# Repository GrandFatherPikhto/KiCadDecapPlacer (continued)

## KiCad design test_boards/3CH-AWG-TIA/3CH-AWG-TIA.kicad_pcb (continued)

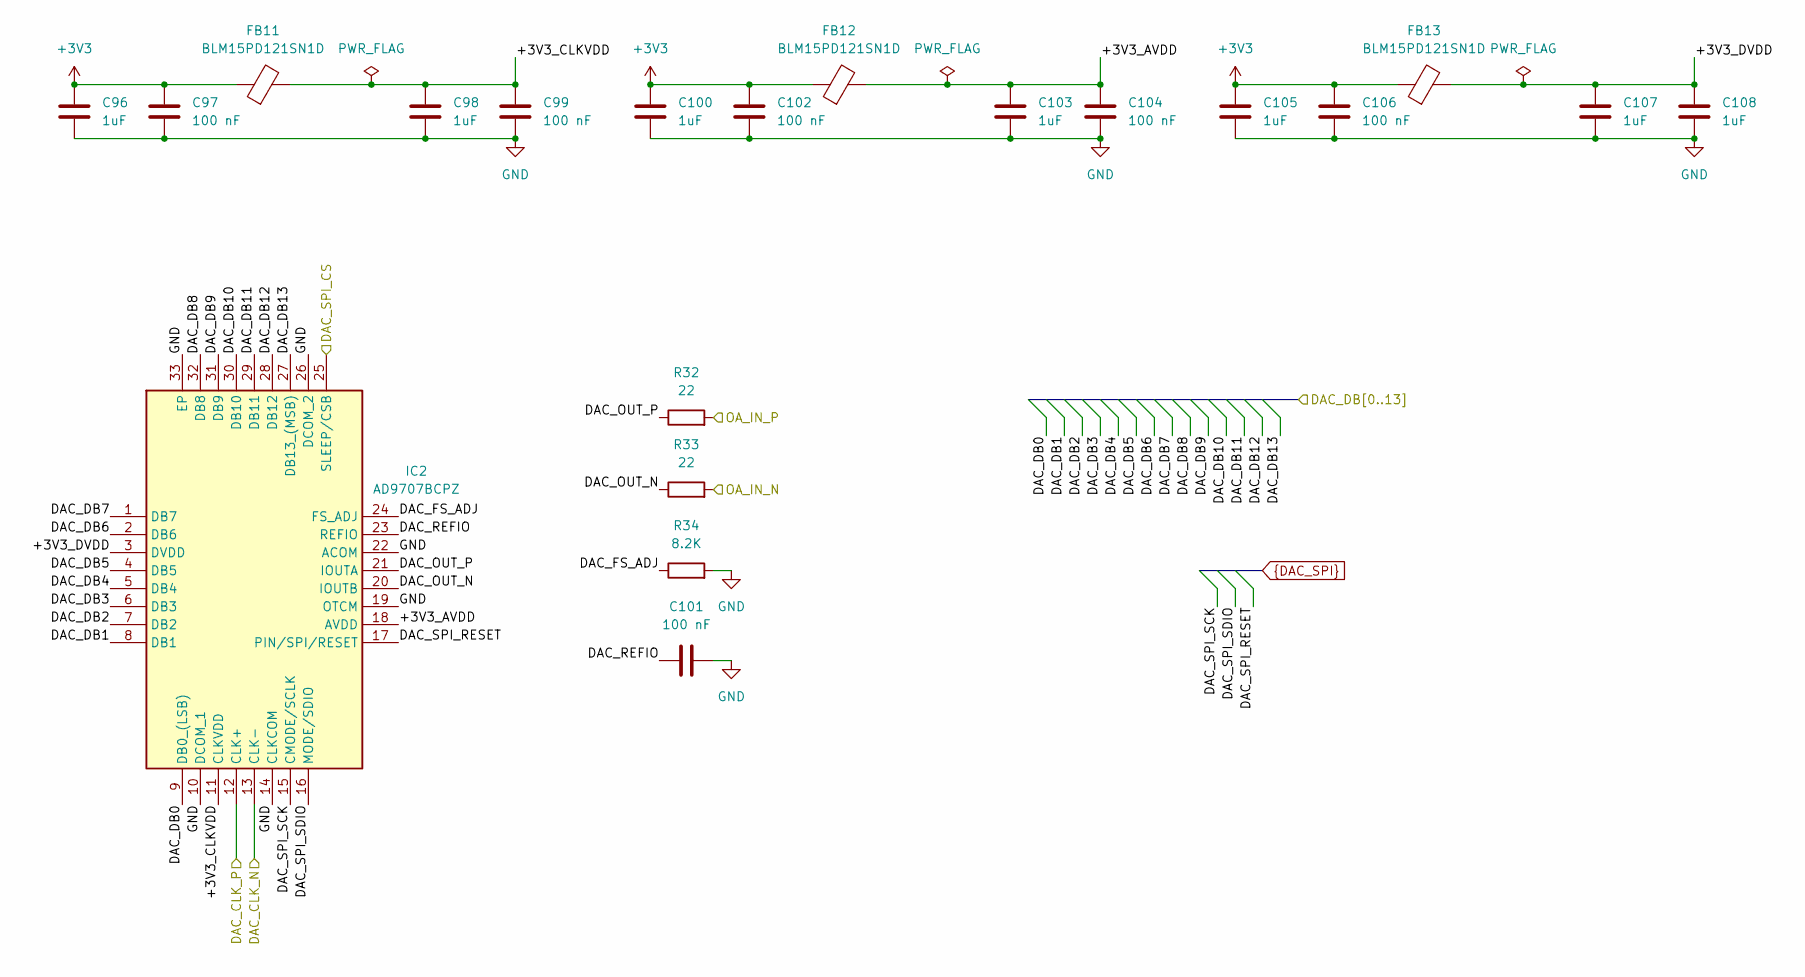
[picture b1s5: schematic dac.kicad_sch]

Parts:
C96, C98, C100, C103, C105, C107, C108: 1uF; C_0603_1608Metric_Pad1.08x0.95mm_HandSolder
C97, C99, C102, C104, C106: 100 nF; C_0402_1005Metric_Pad0.74x0.62mm_HandSolder
C101: 100 nF; C_0603_1608Metric_Pad1.08x0.95mm_HandSolder
FB11, FB12, FB13: BLM15PD121SN1D; L_0402_1005Metric
IC2: AD9707BCPZ; QFN50P500X500X80-33N-D; Manufacturer_Part_Number AD9705BCPZ; Mouser Part Number 584-AD9705BCPZ
R32, R33: 22; R_0402_1005Metric_Pad0.72x0.64mm_HandSolder
R34: 8.2K; R_0402_1005Metric_Pad0.72x0.64mm_HandSolder

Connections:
+3V3: C96.1, C97.1, C100.1, C102.1, C105.1, C106.1, FB11.1, FB12.1, FB13.1; also elsewhere on the board
/Channel_0/DAC/+3V3_AVDD: C103.1, C104.1, FB12.2, IC2.18 (AVDD)
/Channel_0/DAC/+3V3_CLKVDD: C98.1, C99.1, FB11.2, IC2.11 (CLKVDD)
/Channel_0/DAC/+3V3_DVDD: C107.1, C108.1, FB13.2, IC2.3 (DVDD)
/Channel_0/DAC/DAC_FS_ADJ: IC2.24 (FS_ADJ), R34.1
/Channel_0/DAC/DAC_OUT_N: IC2.20 (IOUTB), R33.1
/Channel_0/DAC/DAC_OUT_P: IC2.21 (IOUTA), R32.1
/Channel_0/DAC/DAC_REFIO: C101.1, IC2.23 (REFIO)
/Channel_0/DAC_CLK_N: IC2.13 (CLK-); also elsewhere on the board
/Channel_0/DAC_CLK_P: IC2.12 (CLK+); also elsewhere on the board
/Channel_0/DAC_DB0: IC2.9 (DB0_(LSB)); also elsewhere on the board
/Channel_0/DAC_DB1: IC2.8 (DB1); also elsewhere on the board
/Channel_0/DAC_DB2: IC2.7 (DB2); also elsewhere on the board
/Channel_0/DAC_DB3: IC2.6 (DB3); also elsewhere on the board
/Channel_0/DAC_DB4: IC2.5 (DB4); also elsewhere on the board
/Channel_0/DAC_DB5: IC2.4 (DB5); also elsewhere on the board
/Channel_0/DAC_DB6: IC2.2 (DB6); also elsewhere on the board
/Channel_0/DAC_DB7: IC2.1 (DB7); also elsewhere on the board
/Channel_0/DAC_DB8: IC2.32 (DB8); also elsewhere on the board
/Channel_0/DAC_DB9: IC2.31 (DB9); also elsewhere on the board
/Channel_0/DAC_DB10: IC2.30 (DB10); also elsewhere on the board
/Channel_0/DAC_DB11: IC2.29 (DB11); also elsewhere on the board
/Channel_0/DAC_DB12: IC2.28 (DB12); also elsewhere on the board
/Channel_0/DAC_DB13: IC2.27 (DB13_(MSB)); also elsewhere on the board
/Channel_0/OpAmp/OA_IN_N: R33.2; also elsewhere on the board
/Channel_0/OpAmp/OA_IN_P: R32.2; also elsewhere on the board
/FPGA/DAC0_SPI_CS: IC2.25 (SLEEP/CSB); also elsewhere on the board
DAC_SPI_RESET: IC2.17 (PIN/SPI/RESET); also elsewhere on the board
DAC_SPI_SCK: IC2.15 (CMODE/SCLK); also elsewhere on the board
DAC_SPI_SDIO: IC2.16 (MODE/SDIO); also elsewhere on the board
GND: C96.2, C97.2, C98.2, C99.2, C100.2, C101.2, C102.2, C103.2, C104.2, C105.2, C106.2, C107.2, C108.2, IC2.10 (DCOM_1), IC2.14 (CLKCOM), IC2.19 (OTCM), IC2.22 (ACOM), IC2.26 (DCOM_2), IC2.33 (EP), R34.2; also elsewhere on the board

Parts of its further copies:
C130, C132, C134, C137, C139, C141, C142, C164, C166, C168, C171, C173, C175, C176: 1uF; C_0603_1608Metric_Pad1.08x0.95mm_HandSolder
C131, C133, C136, C138, C140, C165, C167, C170, C172, C174: 100 nF; C_0402_1005Metric_Pad0.74x0.62mm_HandSolder
C135, C169: 100 nF; C_0603_1608Metric_Pad1.08x0.95mm_HandSolder
FB18, FB19, FB20, FB25, FB26, FB27: BLM15PD121SN1D; L_0402_1005Metric
IC3, IC4: AD9707BCPZ; QFN50P500X500X80-33N-D; Manufacturer_Part_Number AD9705BCPZ; Mouser Part Number 584-AD9705BCPZ
R48, R49, R64, R65: 22; R_0402_1005Metric_Pad0.72x0.64mm_HandSolder
R50, R66: 8.2K; R_0402_1005Metric_Pad0.72x0.64mm_HandSolder

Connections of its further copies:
+3V3: C130.1, C131.1, C134.1, C136.1, C139.1, C140.1, C164.1, C165.1, C168.1, C170.1, C173.1, C174.1, FB18.1, FB19.1, FB20.1, FB25.1, FB26.1, FB27.1; also elsewhere on the board
/Channel_1/DAC/+3V3_AVDD: C137.1, C138.1, FB19.2, IC3.18 (AVDD)
/Channel_1/DAC/+3V3_CLKVDD: C132.1, C133.1, FB18.2, IC3.11 (CLKVDD)
/Channel_1/DAC/+3V3_DVDD: C141.1, C142.1, FB20.2, IC3.3 (DVDD)
/Channel_1/DAC/DAC_FS_ADJ: IC3.24 (FS_ADJ), R50.1
/Channel_1/DAC/DAC_OUT_N: IC3.20 (IOUTB), R49.1
/Channel_1/DAC/DAC_OUT_P: IC3.21 (IOUTA), R48.1
/Channel_1/DAC/DAC_REFIO: C135.1, IC3.23 (REFIO)
/Channel_1/DAC_CLK_N: IC3.13 (CLK-); also elsewhere on the board
/Channel_1/DAC_CLK_P: IC3.12 (CLK+); also elsewhere on the board
/Channel_1/DAC_DB0: IC3.9 (DB0_(LSB)); also elsewhere on the board
/Channel_1/DAC_DB1: IC3.8 (DB1); also elsewhere on the board
/Channel_1/DAC_DB2: IC3.7 (DB2); also elsewhere on the board
/Channel_1/DAC_DB3: IC3.6 (DB3); also elsewhere on the board
/Channel_1/DAC_DB4: IC3.5 (DB4); also elsewhere on the board
/Channel_1/DAC_DB5: IC3.4 (DB5); also elsewhere on the board
/Channel_1/DAC_DB6: IC3.2 (DB6); also elsewhere on the board
/Channel_1/DAC_DB7: IC3.1 (DB7); also elsewhere on the board
/Channel_1/DAC_DB8: IC3.32 (DB8); also elsewhere on the board
/Channel_1/DAC_DB9: IC3.31 (DB9); also elsewhere on the board
/Channel_1/DAC_DB10: IC3.30 (DB10); also elsewhere on the board
/Channel_1/DAC_DB11: IC3.29 (DB11); also elsewhere on the board
/Channel_1/DAC_DB12: IC3.28 (DB12); also elsewhere on the board
/Channel_1/DAC_DB13: IC3.27 (DB13_(MSB)); also elsewhere on the board
/Channel_1/OpAmp/OA_IN_N: R49.2; also elsewhere on the board
/Channel_1/OpAmp/OA_IN_P: R48.2; also elsewhere on the board
/Channel_2/DAC/+3V3_AVDD: C171.1, C172.1, FB26.2, IC4.18 (AVDD)
/Channel_2/DAC/+3V3_CLKVDD: C166.1, C167.1, FB25.2, IC4.11 (CLKVDD)
/Channel_2/DAC/+3V3_DVDD: C175.1, C176.1, FB27.2, IC4.3 (DVDD)
/Channel_2/DAC/DAC_FS_ADJ: IC4.24 (FS_ADJ), R66.1
/Channel_2/DAC/DAC_OUT_N: IC4.20 (IOUTB), R65.1
/Channel_2/DAC/DAC_OUT_P: IC4.21 (IOUTA), R64.1
/Channel_2/DAC/DAC_REFIO: C169.1, IC4.23 (REFIO)
/Channel_2/DAC_CLK_N: IC4.13 (CLK-); also elsewhere on the board
/Channel_2/DAC_CLK_P: IC4.12 (CLK+); also elsewhere on the board
/Channel_2/DAC_DB0: IC4.9 (DB0_(LSB)); also elsewhere on the board
/Channel_2/DAC_DB1: IC4.8 (DB1); also elsewhere on the board
/Channel_2/DAC_DB2: IC4.7 (DB2); also elsewhere on the board
/Channel_2/DAC_DB3: IC4.6 (DB3); also elsewhere on the board
/Channel_2/DAC_DB4: IC4.5 (DB4); also elsewhere on the board
/Channel_2/DAC_DB5: IC4.4 (DB5); also elsewhere on the board
/Channel_2/DAC_DB6: IC4.2 (DB6); also elsewhere on the board
/Channel_2/DAC_DB7: IC4.1 (DB7); also elsewhere on the board
/Channel_2/DAC_DB8: IC4.32 (DB8); also elsewhere on the board
/Channel_2/DAC_DB9: IC4.31 (DB9); also elsewhere on the board
/Channel_2/DAC_DB10: IC4.30 (DB10); also elsewhere on the board
/Channel_2/DAC_DB11: IC4.29 (DB11); also elsewhere on the board
/Channel_2/DAC_DB12: IC4.28 (DB12); also elsewhere on the board
/Channel_2/DAC_DB13: IC4.27 (DB13_(MSB)); also elsewhere on the board
/Channel_2/OpAmp/OA_IN_N: R65.2; also elsewhere on the board
/Channel_2/OpAmp/OA_IN_P: R64.2; also elsewhere on the board
/FPGA/DAC1_SPI_CS: IC3.25 (SLEEP/CSB); also elsewhere on the board
/FPGA/DAC2_SPI_CS: IC4.25 (SLEEP/CSB); also elsewhere on the board
DAC_SPI_RESET: IC3.17 (PIN/SPI/RESET), IC4.17 (PIN/SPI/RESET); also elsewhere on the board
DAC_SPI_SCK: IC3.15 (CMODE/SCLK), IC4.15 (CMODE/SCLK); also elsewhere on the board
DAC_SPI_SDIO: IC3.16 (MODE/SDIO), IC4.16 (MODE/SDIO); also elsewhere on the board
GND: C130.2, C131.2, C132.2, C133.2, C134.2, C135.2, C136.2, C137.2, C138.2, C139.2, C140.2, C141.2, C142.2, C164.2, C165.2, C166.2, C167.2, C168.2, C169.2, C170.2, C171.2, C172.2, C173.2, C174.2, C175.2, C176.2, IC3.10 (DCOM_1), IC3.14 (CLKCOM), IC3.19 (OTCM), IC3.22 (ACOM), IC3.26 (DCOM_2), IC3.33 (EP), IC4.10 (DCOM_1), IC4.14 (CLKCOM), IC4.19 (OTCM), IC4.22 (ACOM), IC4.26 (DCOM_2), IC4.33 (EP), R50.2, R66.2; also elsewhere on the board

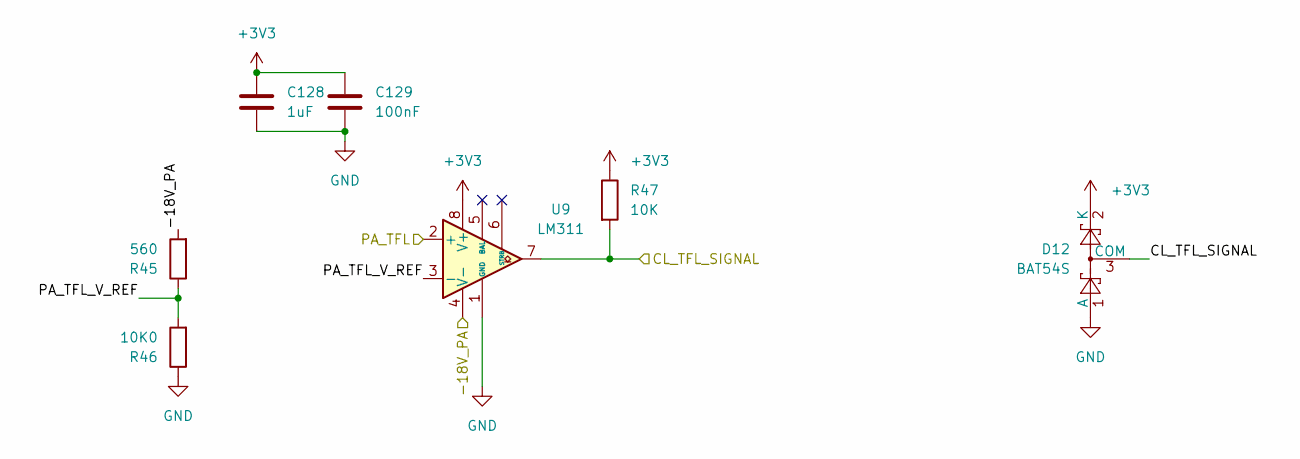
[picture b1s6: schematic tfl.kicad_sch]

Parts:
C128: 1uF; C_0603_1608Metric_Pad1.08x0.95mm_HandSolder
C129: 100nF; C_0603_1608Metric_Pad1.08x0.95mm_HandSolder
D12: BAT54S; SOT-23
R45: 560; R_0402_1005Metric_Pad0.72x0.64mm_HandSolder
R46: 10K0; R_0402_1005Metric_Pad0.72x0.64mm_HandSolder
R47: 10K; R_0603_1608Metric_Pad0.98x0.95mm_HandSolder
U9: LM311; SOIC-8_3.9x4.9mm_P1.27mm

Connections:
+3V3: C128.1, C129.1, D12.2 (K), R47.1, U9.8 (V+); also elsewhere on the board
/Channel_0/Power Amplifier Sheet/-18V_PA: R45.2, U9.4 (V-); also elsewhere on the board
/Channel_0/Power Amplifier Sheet/PA_TFL: U9.2 (+); also elsewhere on the board
/Channel_0/TFL/CL_TFL_SIGNAL: D12.3 (COM), R47.2, U9.7; also elsewhere on the board
/Channel_0/TFL/PA_TFL_V_REF: R45.1, R46.2, U9.3 (-)
GND: C128.2, C129.2, D12.1 (A), R46.1, U9.1 (GND); also elsewhere on the board

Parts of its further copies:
C162, C196: 1uF; C_0603_1608Metric_Pad1.08x0.95mm_HandSolder
C163, C197: 100nF; C_0603_1608Metric_Pad1.08x0.95mm_HandSolder
D15, D18: BAT54S; SOT-23
R61, R77: 560; R_0402_1005Metric_Pad0.72x0.64mm_HandSolder
R62, R78: 10K0; R_0402_1005Metric_Pad0.72x0.64mm_HandSolder
R63, R79: 10K; R_0603_1608Metric_Pad0.98x0.95mm_HandSolder
U13, U17: LM311; SOIC-8_3.9x4.9mm_P1.27mm

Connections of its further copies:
+3V3: C162.1, C163.1, C196.1, C197.1, D15.2 (K), D18.2 (K), R63.1, R79.1, U13.8 (V+), U17.8 (V+); also elsewhere on the board
/Channel_1/Power Amplifier Sheet/-18V_PA: R61.2, U13.4 (V-); also elsewhere on the board
/Channel_1/Power Amplifier Sheet/PA_TFL: U13.2 (+); also elsewhere on the board
/Channel_1/TFL/CL_TFL_SIGNAL: D15.3 (COM), R63.2, U13.7; also elsewhere on the board
/Channel_1/TFL/PA_TFL_V_REF: R61.1, R62.2, U13.3 (-)
/Channel_2/Power Amplifier Sheet/-18V_PA: R77.2, U17.4 (V-); also elsewhere on the board
/Channel_2/Power Amplifier Sheet/PA_TFL: U17.2 (+); also elsewhere on the board
/Channel_2/TFL/CL_TFL_SIGNAL: D18.3 (COM), R79.2, U17.7; also elsewhere on the board
/Channel_2/TFL/PA_TFL_V_REF: R77.1, R78.2, U17.3 (-)
GND: C162.2, C163.2, C196.2, C197.2, D15.1 (A), D18.1 (A), R62.1, R78.1, U13.1 (GND), U17.1 (GND); also elsewhere on the board

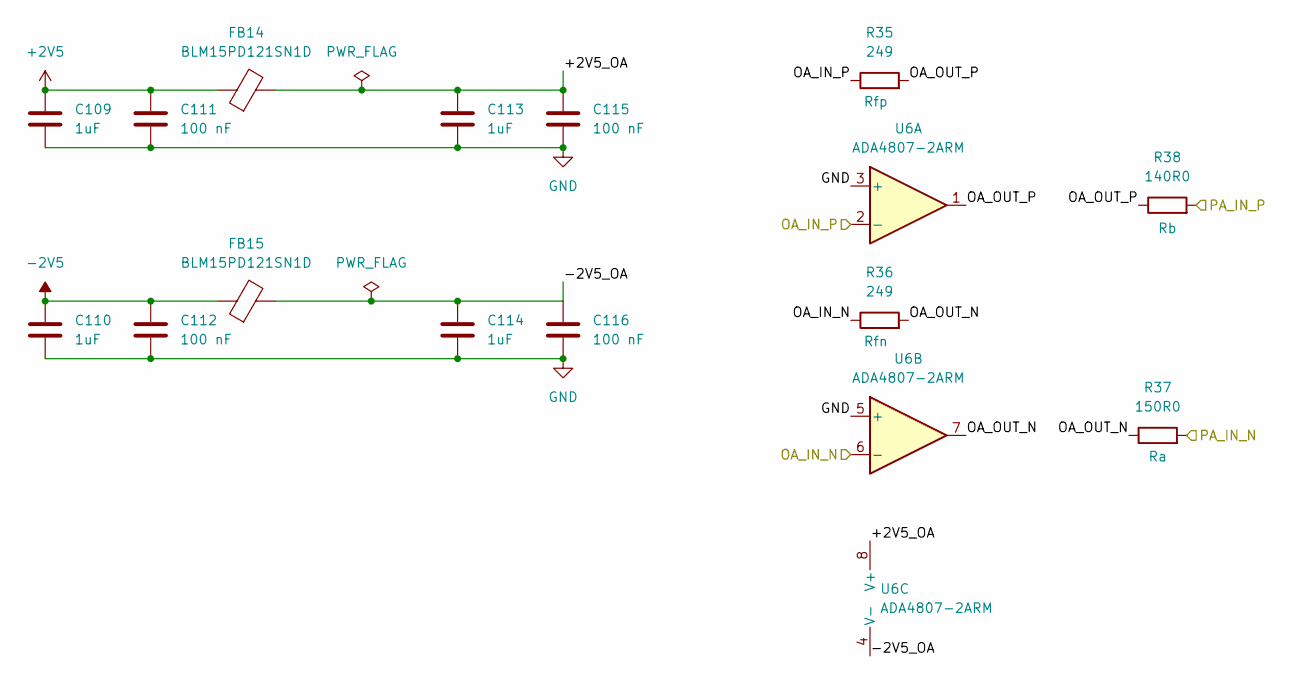
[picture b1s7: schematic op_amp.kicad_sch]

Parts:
C109, C110, C113, C114: 1uF; C_0603_1608Metric_Pad1.08x0.95mm_HandSolder
C111, C112, C115, C116: 100 nF; C_0402_1005Metric_Pad0.74x0.62mm_HandSolder
FB14, FB15: BLM15PD121SN1D; L_0402_1005Metric
R35, R36: 249; R_0402_1005Metric_Pad0.72x0.64mm_HandSolder
R37: 150R0; R_0603_1608Metric_Pad0.98x0.95mm_HandSolder
R38: 140R0; R_0603_1608Metric_Pad0.98x0.95mm_HandSolder
U6: ADA4807-2ARM; MSOP-8_3x3mm_P0.65mm

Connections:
+2V5: C109.1, C111.1, FB14.1; also elsewhere on the board
-2V5: C110.1, C112.1, FB15.1; also elsewhere on the board
/Channel_0/OpAmp/+2V5_OA: C113.1, C115.1, FB14.2, U6.8 (V+)
/Channel_0/OpAmp/-2V5_OA: C114.1, C116.1, FB15.2, U6.4 (V-)
/Channel_0/OpAmp/OA_IN_N: R36.1, U6.6 (-); also elsewhere on the board
/Channel_0/OpAmp/OA_IN_P: R35.1, U6.2 (-); also elsewhere on the board
/Channel_0/OpAmp/OA_OUT_N: R36.2, R37.1, U6.7
/Channel_0/OpAmp/OA_OUT_P: R35.2, R38.1, U6.1
/Channel_0/OpAmp/PA_IN_P: R38.2; also elsewhere on the board
/Channel_0/Power Amplifier Sheet/PA_IN_N: R37.2; also elsewhere on the board
GND: C109.2, C110.2, C111.2, C112.2, C113.2, C114.2, C115.2, C116.2, U6.3 (+), U6.5 (+); also elsewhere on the board

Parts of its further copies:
C143, C144, C147, C148, C177, C178, C181, C182: 1uF; C_0603_1608Metric_Pad1.08x0.95mm_HandSolder
C145, C146, C149, C150, C179, C180, C183, C184: 100 nF; C_0402_1005Metric_Pad0.74x0.62mm_HandSolder
FB21, FB22, FB28, FB29: BLM15PD121SN1D; L_0402_1005Metric
R51, R52, R67, R68: 249; R_0402_1005Metric_Pad0.72x0.64mm_HandSolder
R53, R69: 150R0; R_0603_1608Metric_Pad0.98x0.95mm_HandSolder
R54, R70: 140R0; R_0603_1608Metric_Pad0.98x0.95mm_HandSolder
U10, U14: ADA4807-2ARM; MSOP-8_3x3mm_P0.65mm

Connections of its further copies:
+2V5: C143.1, C145.1, C177.1, C179.1, FB21.1, FB28.1; also elsewhere on the board
-2V5: C144.1, C146.1, C178.1, C180.1, FB22.1, FB29.1; also elsewhere on the board
/Channel_1/OpAmp/+2V5_OA: C147.1, C149.1, FB21.2, U10.8 (V+)
/Channel_1/OpAmp/-2V5_OA: C148.1, C150.1, FB22.2, U10.4 (V-)
/Channel_1/OpAmp/OA_IN_N: R52.1, U10.6 (-); also elsewhere on the board
/Channel_1/OpAmp/OA_IN_P: R51.1, U10.2 (-); also elsewhere on the board
/Channel_1/OpAmp/OA_OUT_N: R52.2, R53.1, U10.7
/Channel_1/OpAmp/OA_OUT_P: R51.2, R54.1, U10.1
/Channel_1/OpAmp/PA_IN_P: R54.2; also elsewhere on the board
/Channel_1/Power Amplifier Sheet/PA_IN_N: R53.2; also elsewhere on the board
/Channel_2/OpAmp/+2V5_OA: C181.1, C183.1, FB28.2, U14.8 (V+)
/Channel_2/OpAmp/-2V5_OA: C182.1, C184.1, FB29.2, U14.4 (V-)
/Channel_2/OpAmp/OA_IN_N: R68.1, U14.6 (-); also elsewhere on the board
/Channel_2/OpAmp/OA_IN_P: R67.1, U14.2 (-); also elsewhere on the board
/Channel_2/OpAmp/OA_OUT_N: R68.2, R69.1, U14.7
/Channel_2/OpAmp/OA_OUT_P: R67.2, R70.1, U14.1
/Channel_2/OpAmp/PA_IN_P: R70.2; also elsewhere on the board
/Channel_2/Power Amplifier Sheet/PA_IN_N: R69.2; also elsewhere on the board
GND: C143.2, C144.2, C145.2, C146.2, C147.2, C148.2, C149.2, C150.2, C177.2, C178.2, C179.2, C180.2, C181.2, C182.2, C183.2, C184.2, U10.3 (+), U10.5 (+), U14.3 (+), U14.5 (+); also elsewhere on the board

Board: 4 copper layers, 353 parts (0 on the bottom side), 182 nets, no tracks yet.

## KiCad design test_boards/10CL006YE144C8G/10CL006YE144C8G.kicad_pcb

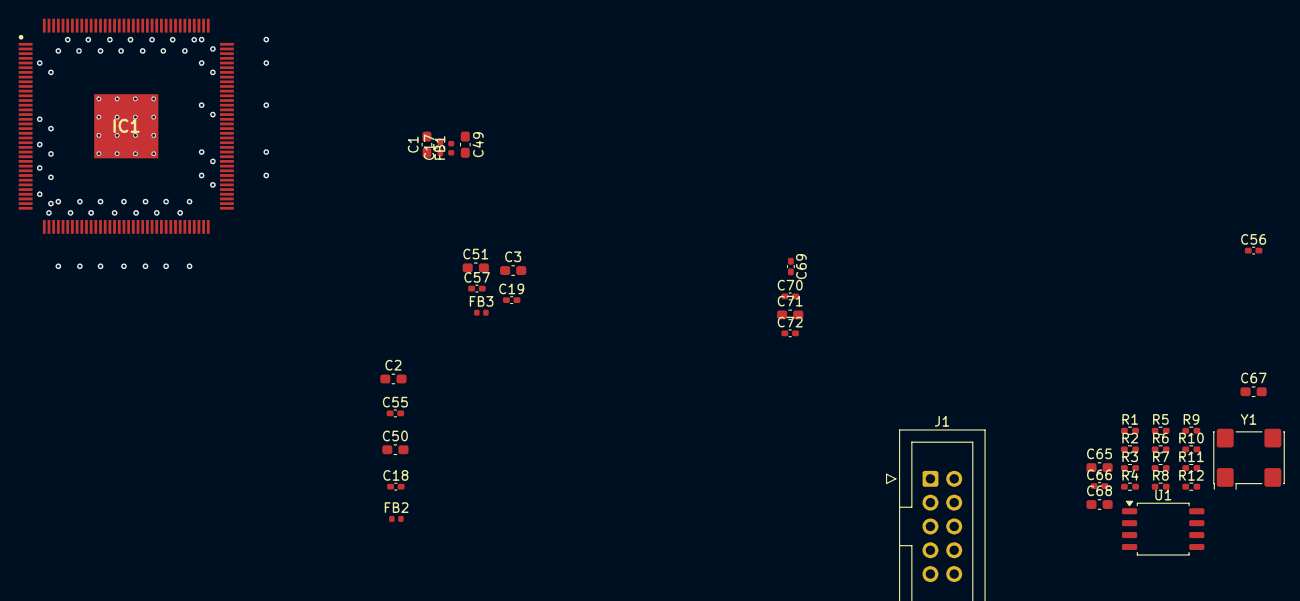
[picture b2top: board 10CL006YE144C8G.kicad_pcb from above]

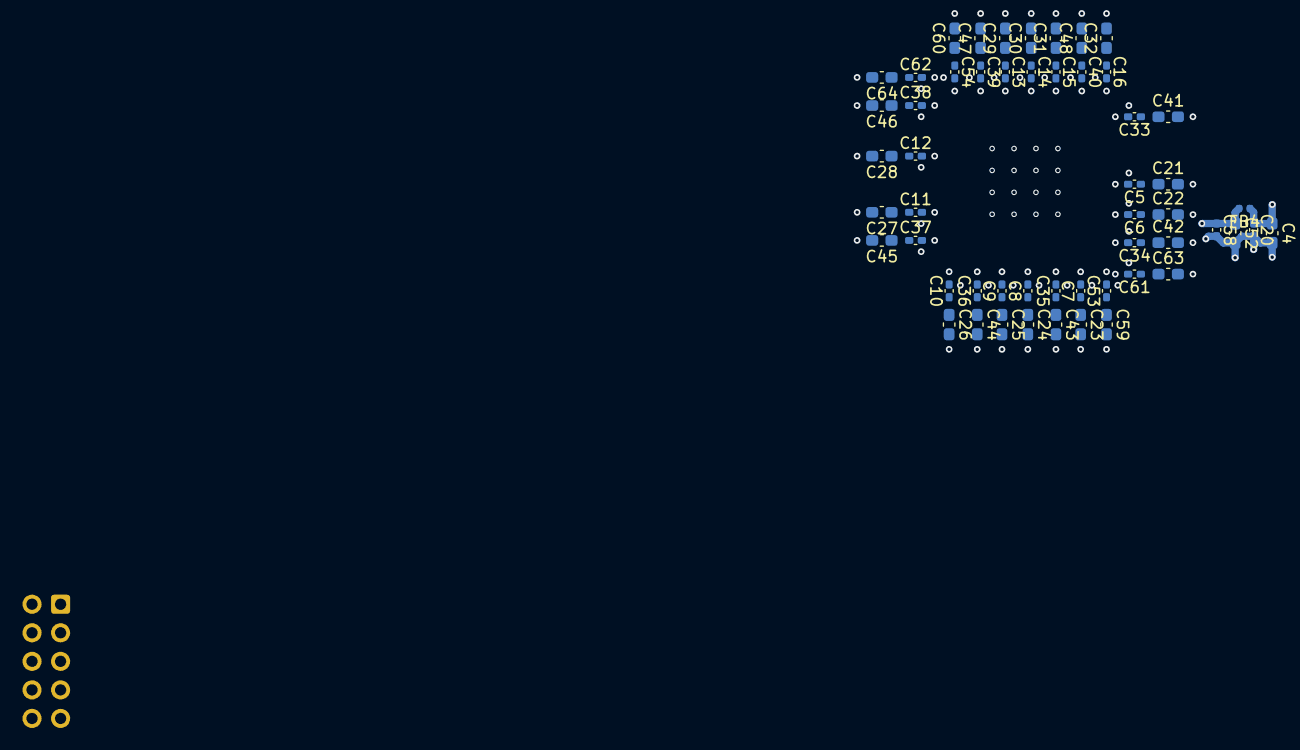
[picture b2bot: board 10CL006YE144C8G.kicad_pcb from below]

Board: 2 copper layers, 92 parts (53 on the bottom side), 26 nets.

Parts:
C1, C2, C3, C4, C49, C50, C51, C52, C65, C67, C68, C71: 1uF; C_0603_1608Metric_Pad1.08x0.95mm_HandSolder
C5, C6, C7, C8, C9, C10, C11, C12, C13, C14, C15, C16, C17, C18, C19, C20, C33, C34, C35, C36, C37, C38, C39, C40, C53, C54, C55, C56, C57, C58, C61, C62, C66, C69, C70, C72: 100 nF; C_0402_1005Metric_Pad0.74x0.62mm_HandSolder
C21, C22, C23, C24, C25, C26, C27, C28, C29, C30, C31, C32, C41, C42, C43, C44, C45, C46, C47, C48, C59, C60, C63, C64: 4.7 uF; C_0603_1608Metric_Pad1.08x0.95mm_HandSolder
FB1, FB2, FB3, FB4: BLM15PD121SN1D; L_0402_1005Metric
IC1: 10CL006YE144C8G; QFP50P2200X2200X165-145N
J1: CL_JTAG; IDC-Header_2x05_P2.54mm_Vertical
R1: 1K; R_0402_1005Metric_Pad0.72x0.64mm_HandSolder
R2, R4, R5, R7: 2R2; R_0402_1005Metric_Pad0.72x0.64mm_HandSolder
R3: 33; R_0402_1005Metric_Pad0.72x0.64mm_HandSolder
R6, R11, R12: 4.7K; R_0402_1005Metric_Pad0.72x0.64mm_HandSolder
R8, R9, R10: 10K; R_0402_1005Metric_Pad0.72x0.64mm_HandSolder
U1: W25Q128JVS; SOIC-8_5.3x5.3mm_P1.27mm
Y1: SG-7050CAN; Oscillator_SMD_SeikoEpson_SG8002CA-4Pin_7.0x5.0mm

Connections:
+1V2: C1.1, C2.1, C17.1, C18.1, FB1.1, FB2.1
+1V2_VCCD_PLL: C50.1, C53.1, C54.1, C55.1, C59.1, C60.1, FB2.2, IC1.37 (VCCD_PLL1), IC1.109 (VCCD_PLL2)
+1V2_VCCINT: C33.1, C34.1, C35.1, C36.1, C37.1, C38.1, C39.1, C40.1, C41.1, C42.1, C43.1, C44.1, C45.1, C46.1, C47.1, C48.1, C49.1, C56.1, FB1.2, IC1.5 (VCCINT_1), IC1.29 (VCCINT_2), IC1.45 (VCCINT_3), IC1.61 (VCCINT_4), IC1.78 (VCCINT_5), IC1.102 (VCCINT_6), IC1.116 (VCCINT_7), IC1.134 (VCCINT_8)
+2V5: C3.1, C19.1, FB3.1
+2V5_VCCA: C51.1, C57.1, C61.1, C62.1, C63.1, C64.1, FB3.2, IC1.35 (VCCA1), IC1.96 (MSEL1), IC1.107 (VCCA2)
+3V3: C4.1, C20.1, C65.1, C66.1, C67.1, C69.1, FB4.1, R4.1, R7.1
+3V3_FLASH: C71.1, C72.2, R2.2, R5.2, R7.2, U1.8 (VCC)
+3V3_OSCILL: C68.1, C70.2, R1.1, R4.2, Y1.4 (VCC)
+3V3_VCCIO: C5.1, C6.1, C7.1, C8.1, C9.1, C10.1, C11.1, C12.1, C13.1, C14.1, C15.1, C16.1, C21.1, C22.1, C23.1, C24.1, C25.1, C26.1, C27.1, C28.1, C29.1, C30.1, C31.1, C32.1, C52.1, C58.1, FB4.2, IC1.17 (VCCIO1), IC1.26 (VCCIO2), IC1.40 (VCCIO3_1), IC1.47 (VCCIO3_2), IC1.56 (VCCIO4_1), IC1.62 (VCCIO4_2), IC1.81 (VCCIO5), IC1.93 (VCCIO6), IC1.117 (VCCIO7_1), IC1.122 (VCCIO7_2), IC1.130 (VCCIO8_1), IC1.139 (VCCIO8_2), J1.4, R8.2, R9.2, R10.2, R11.2, R12.2
/CL_ASDO: IC1.6 (IO_4), U1.5 (DI/IO_{0})
/CL_CLK_0: R3.1, Y1.3 (OUT)
/CL_CLK_0_IN: IC1.22 (CLK0), R3.2
/CL_CLK_ON: R1.2, Y1.1 (~ST)
/CL_CONFIG_DONE: IC1.92 (CONF_DONE), R8.1
/CL_DATA0: IC1.13 (IO_10), U1.2 (DO/IO_{1})
/CL_DCLK: IC1.12 (IO_9), U1.6 (CLK)
/CL_NCONFIG: IC1.14 (NCONFIG), R10.1
/CL_NCSO: IC1.8 (IO_6), U1.1 (~CS)
/CL_NSTATUS: IC1.9 (NSTATUS), R9.1
/CL_TCK: IC1.16 (TCK), J1.1, R6.1
/CL_TDI: IC1.15 (TDI), J1.9, R12.1
/CL_TDO: IC1.20 (TDO), J1.3
/CL_TMS: IC1.18 (TMS), J1.5, R11.1
/FL_HOLD: R2.1, U1.7 (~HOLD/~RESET/IO_{3})
/FL_WP: R5.1, U1.3 (~WP/IO_{2})
GND: C1.2, C2.2, C3.2, C4.2, C5.2, C6.2, C7.2, C8.2, C9.2, C10.2, C11.2, C12.2, C13.2, C14.2, C15.2, C16.2, C17.2, C18.2, C19.2, C20.2, C21.2, C22.2, C23.2, C24.2, C25.2, C26.2, C27.2, C28.2, C29.2, C30.2, C31.2, C32.2, C33.2, C34.2, C35.2, C36.2, C37.2, C38.2, C39.2, C40.2, C41.2, C42.2, C43.2, C44.2, C45.2, C46.2, C47.2, C48.2, C49.2, C50.2, C51.2, C52.2, C53.2, C54.2, C55.2, C56.2, C57.2, C58.2, C59.2, C60.2, C61.2, C62.2, C63.2, C64.2, C65.2, C66.2, C67.2, C68.2, C69.2, C70.1, C71.2, C72.1, IC1.4 (GND_1), IC1.19 (GND_2), IC1.21 (NCE), IC1.27 (GND_3), IC1.30 (GND_4), IC1.36 (GNDA1), IC1.41 (GND_5), IC1.48 (GND_6), IC1.57 (GND_7), IC1.63 (GND_8), IC1.64 (GND_9), IC1.79 (GND_10), IC1.82 (GND_11), IC1.94 (MSEL0), IC1.95 (GND_12), IC1.97 (MSEL2), IC1.104 (GND_13), IC1.108 (GNDA2), IC1.110 (GND_14), IC1.118 (GND_15), IC1.123 (GND_16), IC1.131 (GND_17), IC1.140 (GND_18), IC1.145 (EP_(GND)), J1.2, J1.10, R6.2, U1.4 (GND), Y1.2 (GND)
